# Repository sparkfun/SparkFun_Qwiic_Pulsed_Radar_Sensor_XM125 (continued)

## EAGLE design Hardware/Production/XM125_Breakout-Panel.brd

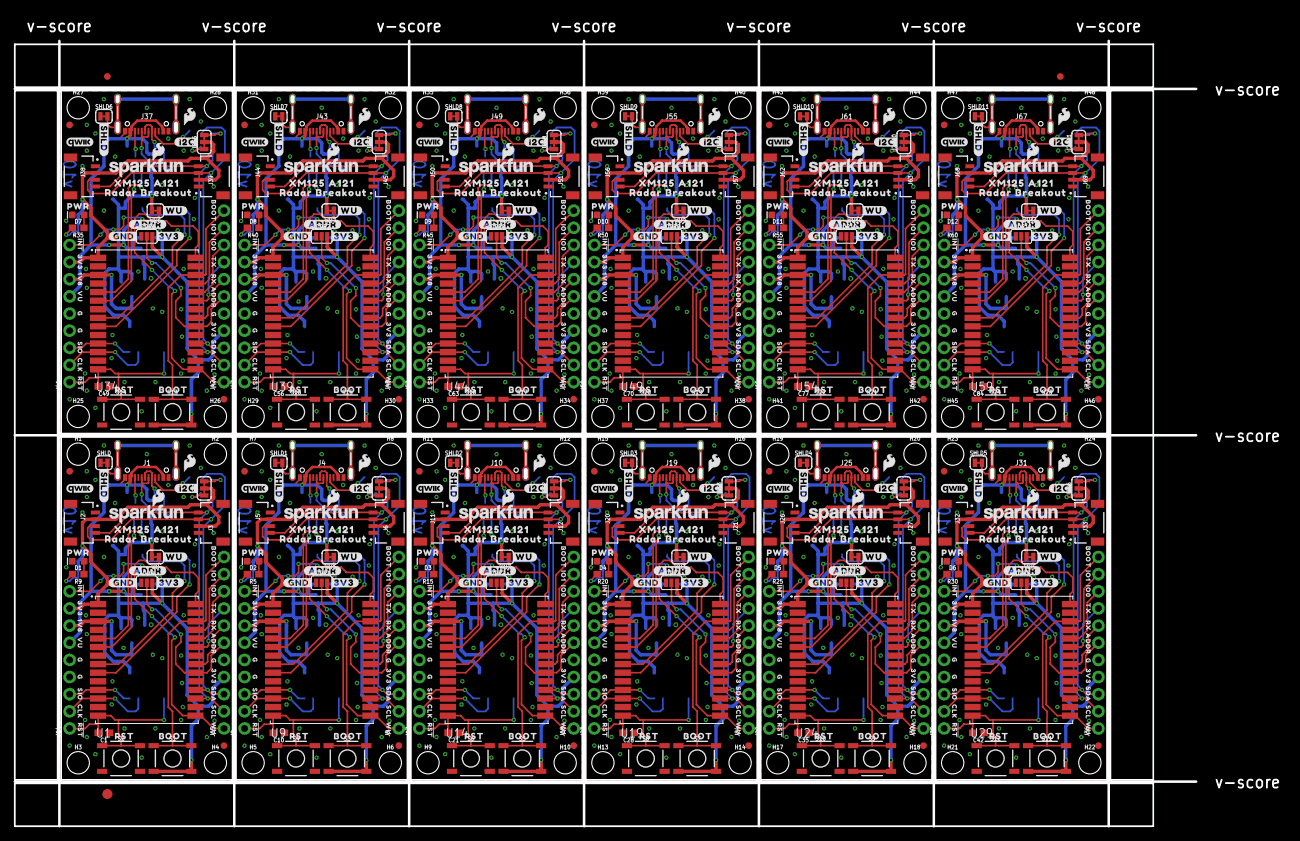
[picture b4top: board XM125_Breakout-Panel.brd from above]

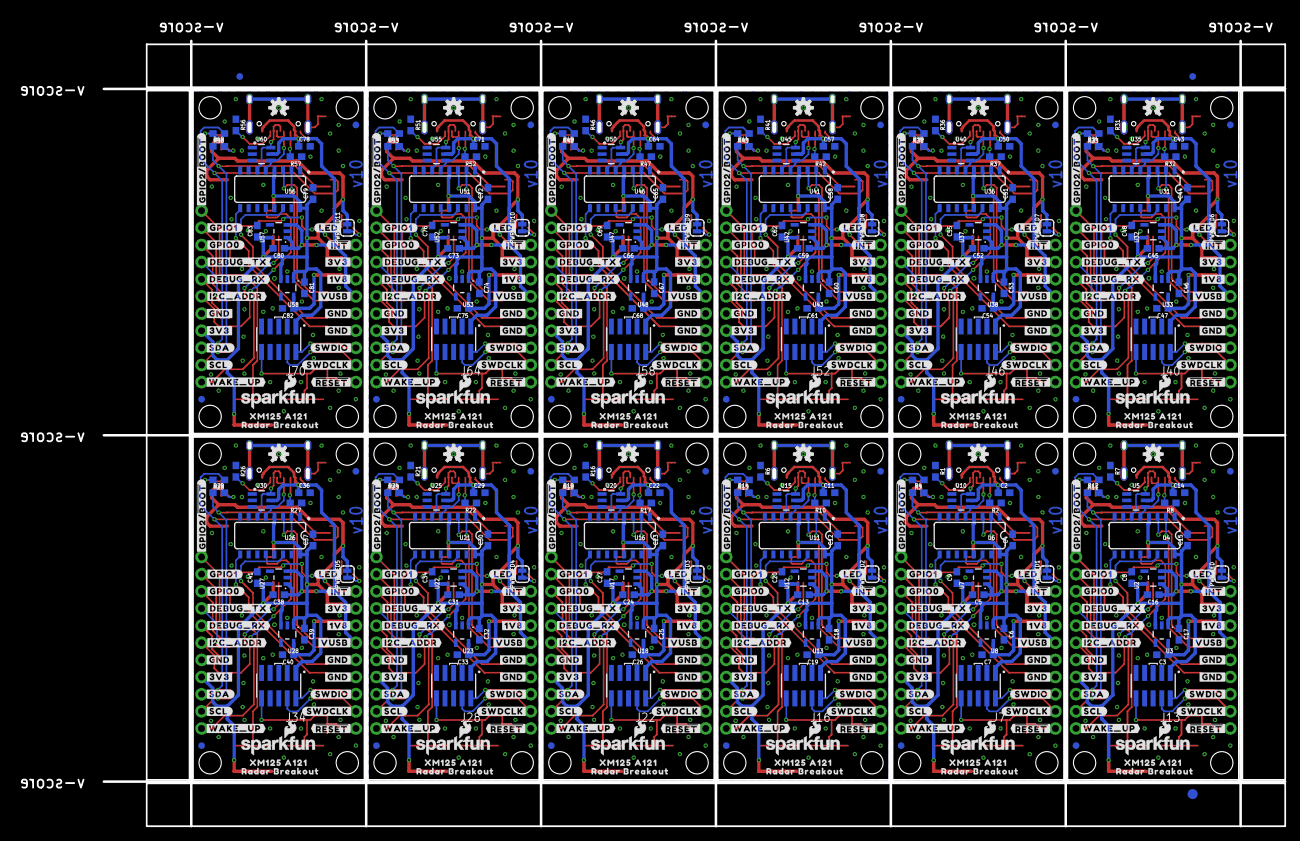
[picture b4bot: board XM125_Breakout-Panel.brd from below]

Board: 2 copper layers, 175.0 x 116.3 mm, 1182 parts (519 on the bottom side), 360 nets.

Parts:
ADDR, ADDR1, ADDR2, ADDR3, ADDR4, ADDR5, ADDR6, ADDR7, ADDR8, ADDR9, ADDR10, ADDR11: JUMPER-SMT_3_NO_SILK; SMT-JUMPER_3_NO_SILK
C1, C2, C4, C10, C11, C12, C14, C15, C21, C22, C23, C28, C29, C30, C35, C36, C37, C42, C43, C44, C49, C50, C51, C56, C57, C58, C63, C64, C65, C70, C71, C72, C77, C78, C79, C84: 0.1uF; 0603
C3, C7, C8, C9, C19, C20, C26, C27, C33, C34, C40, C41, C47, C48, C54, C55, C61, C62, C68, C69, C75, C76, C82, C83: 22uF; 0603
C5, C6, C13, C16, C17, C18, C24, C25, C31, C32, C38, C39, C45, C46, C52, C53, C59, C60, C66, C67, C73, C74, C80, C81: 2.2uF; 0603
D1, D2, D3, D4, D5, D6, D7, D8, D9, D10, D11, D12: Red; LED-0603
E$1, E$2, E$3, E$4: FIDUCIAL-1X2
E$5, E$6: FIDUCIAL-1.5X3
FD1, FD2, FD3, FD4, FD5, FD6, FD7, FD8, FD9, FD10, FD11, FD12, FD13, FD14, FD15, FD16, FD17, FD18, FD19, FD20, FD21, FD22, FD23, FD24, FD25, FD26, FD27, FD28, FD29, FD30, FD31, FD32, FD33, FD34, FD35, FD36, FD37, FD38, FD39, FD40, FD41, FD42, FD43, FD44, FD45, FD46, FD47, FD48: FIDUCIAL1X2; FIDUCIAL-1X2
H1, H2, H3, H4, H5, H6, H7, H8, H9, H10, H11, H12, H13, H14, H15, H16, H17, H18, H19, H20, H21, H22, H23, H24, H25, H26, H27, H28, H29, H30, H31, H32, H33, H34, H35, H36, H37, H38, H39, H40, H41, H42, H43, H44, H45, H46, H47, H48: STAND-OFF
I2C, I2C1, I2C2, I2C3, I2C4, I2C5, I2C6, I2C7, I2C8, I2C9, I2C10, I2C11: JUMPER-SMT_3_2-NC_TRACE_SILK; SMT-JUMPER_3_2-NC_TRACE_SILK
J1, J4, J10, J19, J25, J31, J37, J43, J49, J55, J61, J67: USB-C-16P-2LAYER-PADS
J2, J3, J5, J6, J11, J12, J20, J21, J26, J27, J32, J33, J38, J39, J44, J45, J50, J51, J56, J57, J62, J63, J68, J69: RIGHT_ANGLE; JST04_1MM_RA
J7, J13, J16, J22, J28, J34, J40, J46, J52, J58, J64, J70: SWD (DNP); 2X5-SMD-UNSHROUDED_DNP_NO_PASTE
J8, J14, J17, J23, J29, J35, J41, J47, J53, J59, J65, J71: 1X09_NO_SILK
J9, J15, J18, J24, J30, J36, J42, J48, J54, J60, J66, J72: 1X11_NO_SILK
LOGO1, LOGO2, LOGO11, LOGO16, LOGO21, LOGO26, LOGO31, LOGO36, LOGO41, LOGO46, LOGO51, LOGO56: QWIIC_LOGO_4MM; QWIIC_4MM
LOGO3, LOGO6, LOGO7, LOGO10, LOGO12, LOGO15, LOGO17, LOGO20, LOGO22, LOGO25, LOGO27, LOGO30, LOGO32, LOGO35, LOGO37, LOGO40, LOGO42, LOGO45, LOGO47, LOGO50, LOGO52, LOGO55, LOGO57, LOGO60: SFE_LOGO_NAME_FLAME.1_INCH; SFE_LOGO_NAME_FLAME_.1
LOGO4, LOGO8, LOGO13, LOGO18, LOGO23, LOGO28, LOGO33, LOGO38, LOGO43, LOGO48, LOGO53, LOGO58: OSHW-LOGOS; OSHW-LOGO-S
LOGO5, LOGO9, LOGO14, LOGO19, LOGO24, LOGO29, LOGO34, LOGO39, LOGO44, LOGO49, LOGO54, LOGO59: SFE_LOGO_FLAME.1_INCH; SFE_LOGO_FLAME_.1
PWR_LED, PWR_LED1, PWR_LED2, PWR_LED3, PWR_LED4, PWR_LED5, PWR_LED6, PWR_LED7, PWR_LED8, PWR_LED9, PWR_LED10, PWR_LED11: JUMPER-SMT_2_NC_TRACE_SILK; SMT-JUMPER_2_NC_TRACE_SILK
R1, R2, R6, R7, R8, R10, R16, R17, R21, R22, R26, R27, R31, R32, R36, R37, R41, R42, R46, R47, R51, R52, R56, R57: 5.1k; 0603
R3, R4, R11, R12, R13, R14, R18, R19, R23, R24, R28, R29, R33, R34, R38, R39, R43, R44, R48, R49, R53, R54, R58, R59: 2.2k; 0603
R5, R9, R15, R20, R25, R30, R35, R40, R45, R50, R55, R60: 4.7k; 0603
S1, S2, S3, S4, S5, S6, S7, S8, S9, S10, S11, S12, S13, S14, S15, S16, S17, S18, S19, S20, S21, S22, S23, S24: TACTILE_SWITCH_SMD_5.2MM
SHLD, SHLD1, SHLD2, SHLD3, SHLD4, SHLD5, SHLD6, SHLD7, SHLD8, SHLD9, SHLD10, SHLD11: JUMPER-SMT_2_NC_TRACE_SILK; SMT-JUMPER_2_NC_TRACE_SILK
U1, U9, U14, U19, U24, U29, U34, U39, U44, U49, U54, U59: XM125; XM125_ACC
U2, U7, U12, U17, U22, U27, U32, U37, U42, U47, U52, U57: RT9080-33GJ5; SOT23-5
U3, U8, U13, U18, U23, U28, U33, U38, U43, U48, U53, U58: RT9080-18GJ5; SOT23-5
U4, U6, U11, U16, U21, U26, U31, U36, U41, U46, U51, U56: CH340C; SO016
U5, U10, U15, U20, U25, U30, U35, U40, U45, U50, U55, U60: ESD Diode; SOT-23-6
U$1, U$72, U$126, U$180, U$234, U$288, U$342, U$396, U$450, U$504, U$558, U$612: #INT143
U$2, U$96, U$150, U$204, U$258, U$312, U$366, U$420, U$474, U$528, U$582, U$636: ##INT#2
U$3, U$64, U$118, U$172, U$226, U$280, U$334, U$388, U$442, U$496, U$550, U$604: #LED#139
U$4, U$30, U$31, U$68, U$69, U$70, U$122, U$123, U$124, U$176, U$177, U$178, U$230, U$231, U$232, U$284, U$285, U$286, U$338, U$339, U$340, U$392, U$393, U$394, U$446, U$447, U$448, U$500, U$501, U$502, U$554, U$555, U$556, U$608, U$609, U$610: #GND#141
U$5, U$52, U$110, U$164, U$218, U$272, U$326, U$380, U$434, U$488, U$542, U$596: RST1630063003525
U$6, U$85, U$139, U$193, U$247, U$301, U$355, U$409, U$463, U$517, U$571, U$625: RX1152
U$7, U$97, U$151, U$205, U$259, U$313, U$367, U$421, U$475, U$529, U$583, U$637: #SWDIO#4
U$8, U$95, U$149, U$203, U$257, U$311, U$365, U$419, U$473, U$527, U$581, U$635: #VUSB#1
U$9, U$105, U$159, U$213, U$267, U$321, U$375, U$429, U$483, U$537, U$591, U$645: #3V3#17
U$10, U$58, U$112, U$166, U$220, U$274, U$328, U$382, U$436, U$490, U$544, U$598: #SCL#8
U$11, U$37, U$109, U$163, U$217, U$271, U$325, U$379, U$433, U$487, U$541, U$595: BOOT21630063003532
U$12, U$57, U$111, U$165, U$219, U$273, U$327, U$381, U$435, U$489, U$543, U$597: PWR21630063003533
U$13, U$59, U$113, U$167, U$221, U$275, U$329, U$383, U$437, U$491, U$545, U$599: #SDA#9
U$14, U$33, U$73, U$75, U$127, U$129, U$181, U$183, U$235, U$237, U$289, U$291, U$343, U$345, U$397, U$399, U$451, U$453, U$505, U$507, U$559, U$561, U$613, U$615: 3V3144
U$15, U$74, U$128, U$182, U$236, U$290, U$344, U$398, U$452, U$506, U$560, U$614: 1V8144
U$16, U$67, U$121, U$175, U$229, U$283, U$337, U$391, U$445, U$499, U$553, U$607: #1V8#141
U$17, U$91, U$145, U$199, U$253, U$307, U$361, U$415, U$469, U$523, U$577, U$631: RADAR_BREAKOUT1163
U$18, U$99, U$153, U$207, U$261, U$315, U$369, U$423, U$477, U$531, U$585, U$639: WU9
U$19, U$98, U$152, U$206, U$260, U$314, U$368, U$422, U$476, U$530, U$584, U$638: #RST6
U$20, U$60, U$114, U$168, U$222, U$276, U$330, U$384, U$438, U$492, U$546, U$600: #GPIO0#5
U$21, U$61, U$115, U$169, U$223, U$277, U$331, U$385, U$439, U$493, U$547, U$601: #GPIO1#5
U$22, U$103, U$157, U$211, U$265, U$319, U$373, U$427, U$481, U$535, U$589, U$643: #WU#14
U$23, U$32, U$66, U$71, U$120, U$125, U$174, U$179, U$228, U$233, U$282, U$287, U$336, U$341, U$390, U$395, U$444, U$449, U$498, U$503, U$552, U$557, U$606, U$611: #3V3#141
U$24, U$92, U$146, U$200, U$254, U$308, U$362, U$416, U$470, U$524, U$578, U$632: XM125_A1211163
U$25, U$104, U$158, U$212, U$266, U$320, U$374, U$428, U$482, U$536, U$590, U$644: #ADDR#16
U$26, U$62, U$116, U$170, U$224, U$278, U$332, U$386, U$440, U$494, U$548, U$602: #I2C#126
U$27, U$65, U$119, U$173, U$227, U$281, U$335, U$389, U$443, U$497, U$551, U$605: #GPIO2##BOOT#141
U$28, U$108, U$162, U$216, U$270, U$324, U$378, U$432, U$486, U$540, U$594, U$648: #DEBUG_RX#19
U$29, U$63, U$117, U$171, U$225, U$279, U$333, U$387, U$441, U$495, U$549, U$603: #SHLD#129
U$34, U$35, U$36, U$76, U$77, U$78, U$130, U$131, U$132, U$184, U$185, U$186, U$238, U$239, U$240, U$292, U$293, U$294, U$346, U$347, U$348, U$400, U$401, U$402, U$454, U$455, U$456, U$508, U$509, U$510, U$562, U$563, U$564, U$616, U$617, U$618: G144
U$38, U$79, U$133, U$187, U$241, U$295, U$349, U$403, U$457, U$511, U$565, U$619: VU146
U$39, U$80, U$134, U$188, U$242, U$296, U$350, U$404, U$458, U$512, U$566, U$620: IO0147
U$40, U$81, U$135, U$189, U$243, U$297, U$351, U$405, U$459, U$513, U$567, U$621: IO1148
U$41, U$82, U$136, U$190, U$244, U$298, U$352, U$406, U$460, U$514, U$568, U$622: BOOT1149
U$42, U$83, U$137, U$191, U$245, U$299, U$353, U$407, U$461, U$515, U$569, U$623: CLK1150
U$43, U$84, U$138, U$192, U$246, U$300, U$354, U$408, U$462, U$516, U$570, U$624: #SWDCLK#1151
U$44, U$86, U$140, U$194, U$248, U$302, U$356, U$410, U$464, U$518, U$572, U$626: TX1153
U$45, U$87, U$141, U$195, U$249, U$303, U$357, U$411, U$465, U$519, U$573, U$627: ADDR1154
U$46, U$88, U$142, U$196, U$250, U$304, U$358, U$412, U$466, U$520, U$574, U$628: SDA1155
U$47, U$89, U$143, U$197, U$251, U$305, U$359, U$413, U$467, U$521, U$575, U$629: SCL1157
U$48, U$100, U$154, U$208, U$262, U$316, U$370, U$424, U$478, U$532, U$586, U$640: #I2C_ADDR#12
U$49, U$90, U$144, U$198, U$252, U$306, U$360, U$414, U$468, U$522, U$576, U$630: SIO1159
U$50, U$106, U$160, U$214, U$268, U$322, U$376, U$430, U$484, U$538, U$592, U$646: #GND#17
U$51, U$107, U$161, U$215, U$269, U$323, U$377, U$431, U$485, U$539, U$593, U$647: #DEBUG_TX#18
U$53, U$93, U$147, U$201, U$255, U$309, U$363, U$417, U$471, U$525, U$579, U$633: RADAR_BREAKOUT1166
U$54, U$94, U$148, U$202, U$256, U$310, U$364, U$418, U$472, U$526, U$580, U$634: XM125_A1211167
U$55, U$101, U$155, U$209, U$263, U$317, U$371, U$425, U$479, U$533, U$587, U$641: #WAKE_UP#12
U$56, U$102, U$156, U$210, U$264, U$318, U$372, U$426, U$480, U$534, U$588, U$642: ##RESET#13
WU, WU1, WU2, WU3, WU4, WU5, WU6, WU7, WU8, WU9, WU10, WU11: JUMPER-SMT_2_NC_TRACE_SILK; SMT-JUMPER_2_NC_TRACE_SILK

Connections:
1.8V: C3.1, J14.7, U1.3, U3.5
1.8V1: C7.1, J8.7, U8.5, U9.3
1.8V2: C19.1, J17.7, U13.5, U14.3
1.8V3: C26.1, J23.7, U18.5, U19.3
1.8V4: C33.1, J29.7, U23.5, U24.3
1.8V5: C40.1, J35.7, U28.5, U29.3
1.8V6: C47.1, J41.7, U33.5, U34.3
1.8V7: C54.1, J47.7, U38.5, U39.3
1.8V8: C61.1, J53.7, U43.5, U44.3
1.8V9: C68.1, J59.7, U48.5, U49.3
1.8V10: C75.1, J65.7, U53.5, U54.3
1.8V11: C82.1, J71.7, U58.5, U59.3
3.3V: ADDR.3, C8.1, C15.1, C17.1, I2C.2, J2.2, J3.2, J13.1, J14.8, J15.4, PWR_LED.2, S1.3, S1.4, U1.1, U2.5, U3.1, U3.3, U4.4, U4.16, WU.2
3.3V1: ADDR1.3, C4.1, C6.1, C9.1, I2C1.2, J5.2, J6.2, J7.1, J8.8, J9.4, PWR_LED1.2, S3.3, S3.4, U6.4, U6.16, U7.5, U8.1, U8.3, U9.1, WU1.2
3.3V2: ADDR2.3, C12.1, C18.1, C20.1, I2C2.2, J11.2, J12.2, J16.1, J17.8, J18.4, PWR_LED2.2, S5.3, S5.4, U11.4, U11.16, U12.5, U13.1, U13.3, U14.1, WU2.2
3.3V3: ADDR3.3, C23.1, C25.1, C27.1, I2C3.2, J20.2, J21.2, J22.1, J23.8, J24.4, PWR_LED3.2, S7.3, S7.4, U16.4, U16.16, U17.5, U18.1, U18.3, U19.1, WU3.2
3.3V4: ADDR4.3, C30.1, C32.1, C34.1, I2C4.2, J26.2, J27.2, J28.1, J29.8, J30.4, PWR_LED4.2, S9.3, S9.4, U21.4, U21.16, U22.5, U23.1, U23.3, U24.1, WU4.2
3.3V5: ADDR5.3, C37.1, C39.1, C41.1, I2C5.2, J32.2, J33.2, J34.1, J35.8, J36.4, PWR_LED5.2, S11.3, S11.4, U26.4, U26.16, U27.5, U28.1, U28.3, U29.1, WU5.2
3.3V6: ADDR6.3, C44.1, C46.1, C48.1, I2C6.2, J38.2, J39.2, J40.1, J41.8, J42.4, PWR_LED6.2, S13.3, S13.4, U31.4, U31.16, U32.5, U33.1, U33.3, U34.1, WU6.2
3.3V7: ADDR7.3, C51.1, C53.1, C55.1, I2C7.2, J44.2, J45.2, J46.1, J47.8, J48.4, PWR_LED7.2, S15.3, S15.4, U36.4, U36.16, U37.5, U38.1, U38.3, U39.1, WU7.2
3.3V8: ADDR8.3, C58.1, C60.1, C62.1, I2C8.2, J50.2, J51.2, J52.1, J53.8, J54.4, PWR_LED8.2, S17.3, S17.4, U41.4, U41.16, U42.5, U43.1, U43.3, U44.1, WU8.2
3.3V9: ADDR9.3, C65.1, C67.1, C69.1, I2C9.2, J56.2, J57.2, J58.1, J59.8, J60.4, PWR_LED9.2, S19.3, S19.4, U46.4, U46.16, U47.5, U48.1, U48.3, U49.1, WU9.2
3.3V10: ADDR10.3, C72.1, C74.1, C76.1, I2C10.2, J62.2, J63.2, J64.1, J65.8, J66.4, PWR_LED10.2, S21.3, S21.4, U51.4, U51.16, U52.5, U53.1, U53.3, U54.1, WU10.2
3.3V11: ADDR11.3, C79.1, C81.1, C83.1, I2C11.2, J68.2, J69.2, J70.1, J71.8, J72.4, PWR_LED11.2, S23.3, S23.4, U56.4, U56.16, U57.5, U58.1, U58.3, U59.1, WU11.2
!XM125_INT: J14.9, U1.28
!XM125_INT1: J8.9, U9.28
!XM125_INT2: J17.9, U14.28
!XM125_INT3: J23.9, U19.28
!XM125_INT4: J29.9, U24.28
!XM125_INT5: J35.9, U29.28
!XM125_INT6: J41.9, U34.28
!XM125_INT7: J47.9, U39.28
!XM125_INT8: J53.9, U44.28
!XM125_INT9: J59.9, U49.28
!XM125_INT10: J65.9, U54.28
!XM125_INT11: J71.9, U59.28
!XM125_RESET: C1.2, J13.10, J14.1, S2.1, S2.2, U1.14
!XM125_RESET1: C10.2, J7.10, J8.1, S4.1, S4.2, U9.14
!XM125_RESET2: C21.2, J16.10, J17.1, S6.1, S6.2, U14.14
!XM125_RESET3: C28.2, J22.10, J23.1, S8.1, S8.2, U19.14
!XM125_RESET4: C35.2, J28.10, J29.1, S10.1, S10.2, U24.14
!XM125_RESET5: C42.2, J34.10, J35.1, S12.1, S12.2, U29.14
!XM125_RESET6: C49.2, J40.10, J41.1, S14.1, S14.2, U34.14
!XM125_RESET7: C56.2, J46.10, J47.1, S16.1, S16.2, U39.14
!XM125_RESET8: C63.2, J52.10, J53.1, S18.1, S18.2, U44.14
!XM125_RESET9: C70.2, J58.10, J59.1, S20.1, S20.2, U49.14
!XM125_RESET10: C77.2, J64.10, J65.1, S22.1, S22.2, U54.14
!XM125_RESET11: C84.2, J70.10, J71.1, S24.1, S24.2, U59.14
CH340-CTS: U1.9, U4.9
CH340-CTS1: U6.9, U9.9
CH340-CTS2: U11.9, U14.9
CH340-CTS3: U16.9, U19.9
CH340-CTS4: U21.9, U24.9
CH340-CTS5: U26.9, U29.9
CH340-CTS6: U31.9, U34.9
CH340-CTS7: U36.9, U39.9
CH340-CTS8: U41.9, U44.9
CH340-CTS9: U46.9, U49.9
CH340-CTS10: U51.9, U54.9
CH340-CTS11: U56.9, U59.9
CH340-RTS: U1.8, U4.14
CH340-RTS1: U6.14, U9.8
CH340-RTS2: U11.14, U14.8
CH340-RTS3: U16.14, U19.8
CH340-RTS4: U21.14, U24.8
CH340-RTS5: U26.14, U29.8
CH340-RTS6: U31.14, U34.8
CH340-RTS7: U36.14, U39.8
CH340-RTS8: U41.14, U44.8
CH340-RTS9: U46.14, U49.8
CH340-RTS10: U51.14, U54.8
CH340-RTS11: U56.14, U59.8
CH340-RX: U1.5, U4.3
CH340-RX1: U6.3, U9.5
CH340-RX2: U11.3, U14.5
CH340-RX3: U16.3, U19.5
CH340-RX4: U21.3, U24.5
CH340-RX5: U26.3, U29.5
CH340-RX6: U31.3, U34.5
CH340-RX7: U36.3, U39.5
CH340-RX8: U41.3, U44.5
CH340-RX9: U46.3, U49.5
CH340-RX10: U51.3, U54.5
CH340-RX11: U56.3, U59.5
CH340-TX: U1.6, U4.2
CH340-TX1: U6.2, U9.6
CH340-TX2: U11.2, U14.6
CH340-TX3: U16.2, U19.6
CH340-TX4: U21.2, U24.6
CH340-TX5: U26.2, U29.6
CH340-TX6: U31.2, U34.6
CH340-TX7: U36.2, U39.6
CH340-TX8: U41.2, U44.6
CH340-TX9: U46.2, U49.6
CH340-TX10: U51.2, U54.6
CH340-TX11: U56.2, U59.6
DEBUG_UART-RX: J15.7, U1.21
DEBUG_UART-RX1: J9.7, U9.21
DEBUG_UART-RX2: J18.7, U14.21
DEBUG_UART-RX3: J24.7, U19.21
DEBUG_UART-RX4: J30.7, U24.21
DEBUG_UART-RX5: J36.7, U29.21
DEBUG_UART-RX6: J42.7, U34.21
DEBUG_UART-RX7: J48.7, U39.21
DEBUG_UART-RX8: J54.7, U44.21
DEBUG_UART-RX9: J60.7, U49.21
DEBUG_UART-RX10: J66.7, U54.21
DEBUG_UART-RX11: J72.7, U59.21
DEBUG_UART-TX: J15.8, U1.23
DEBUG_UART-TX1: J9.8, U9.23
DEBUG_UART-TX2: J18.8, U14.23
DEBUG_UART-TX3: J24.8, U19.23
DEBUG_UART-TX4: J30.8, U24.23
DEBUG_UART-TX5: J36.8, U29.23
DEBUG_UART-TX6: J42.8, U34.23
DEBUG_UART-TX7: J48.8, U39.23
DEBUG_UART-TX8: J54.8, U44.23
DEBUG_UART-TX9: J60.8, U49.23
DEBUG_UART-TX10: J66.8, U54.23
DEBUG_UART-TX11: J72.8, U59.23
GND: ADDR.1, C1.1, C3.2, C8.2, C14.2, C15.2, C16.2, C17.2, D1.C, J1.GND, J1.GND2, J2.1, J3.1, J13.3, J13.5, J13.9, J14.4, J14.5, J15.5, R7.1, R8.1, S2.3, S2.4, SHLD.1, U1.2, U1.4, U1.7, U1.10, U1.13, U1.16, U1.19, U1.22, U1.27, U2.2, U3.2, U4.1, U5.2
GND1: ADDR1.1, C2.2, C4.2, C5.2, C6.2, C7.2, C9.2, C10.1, D2.C, J4.GND, J4.GND2, J5.1, J6.1, J7.3, J7.5, J7.9, J8.4, J8.5, J9.5, R1.1, R2.1, S4.3, S4.4, SHLD1.1, U6.1, U7.2, U8.2, U9.2, U9.4, U9.7, U9.10, U9.13, U9.16, U9.19, U9.22, U9.27, U10.2
GND2: ADDR2.1, C11.2, C12.2, C13.2, C18.2, C19.2, C20.2, C21.1, D3.C, J10.GND, J10.GND2, J11.1, J12.1, J16.3, J16.5, J16.9, J17.4, J17.5, J18.5, R6.1, R10.1, S6.3, S6.4, SHLD2.1, U11.1, U12.2, U13.2, U14.2, U14.4, U14.7, U14.10, U14.13, U14.16, U14.19, U14.22, U14.27, U15.2
GND3: ADDR3.1, C22.2, C23.2, C24.2, C25.2, C26.2, C27.2, C28.1, D4.C, J19.GND, J19.GND2, J20.1, J21.1, J22.3, J22.5, J22.9, J23.4, J23.5, J24.5, R16.1, R17.1, S8.3, S8.4, SHLD3.1, U16.1, U17.2, U18.2, U19.2, U19.4, U19.7, U19.10, U19.13, U19.16, U19.19, U19.22, U19.27, U20.2
GND4: ADDR4.1, C29.2, C30.2, C31.2, C32.2, C33.2, C34.2, C35.1, D5.C, J25.GND, J25.GND2, J26.1, J27.1, J28.3, J28.5, J28.9, J29.4, J29.5, J30.5, R21.1, R22.1, S10.3, S10.4, SHLD4.1, U21.1, U22.2, U23.2, U24.2, U24.4, U24.7, U24.10, U24.13, U24.16, U24.19, U24.22, U24.27, U25.2
GND5: ADDR5.1, C36.2, C37.2, C38.2, C39.2, C40.2, C41.2, C42.1, D6.C, J31.GND, J31.GND2, J32.1, J33.1, J34.3, J34.5, J34.9, J35.4, J35.5, J36.5, R26.1, R27.1, S12.3, S12.4, SHLD5.1, U26.1, U27.2, U28.2, U29.2, U29.4, U29.7, U29.10, U29.13, U29.16, U29.19, U29.22, U29.27, U30.2
GND6: ADDR6.1, C43.2, C44.2, C45.2, C46.2, C47.2, C48.2, C49.1, D7.C, J37.GND, J37.GND2, J38.1, J39.1, J40.3, J40.5, J40.9, J41.4, J41.5, J42.5, R31.1, R32.1, S14.3, S14.4, SHLD6.1, U31.1, U32.2, U33.2, U34.2, U34.4, U34.7, U34.10, U34.13, U34.16, U34.19, U34.22, U34.27, U35.2
GND7: ADDR7.1, C50.2, C51.2, C52.2, C53.2, C54.2, C55.2, C56.1, D8.C, J43.GND, J43.GND2, J44.1, J45.1, J46.3, J46.5, J46.9, J47.4, J47.5, J48.5, R36.1, R37.1, S16.3, S16.4, SHLD7.1, U36.1, U37.2, U38.2, U39.2, U39.4, U39.7, U39.10, U39.13, U39.16, U39.19, U39.22, U39.27, U40.2
GND8: ADDR8.1, C57.2, C58.2, C59.2, C60.2, C61.2, C62.2, C63.1, D9.C, J49.GND, J49.GND2, J50.1, J51.1, J52.3, J52.5, J52.9, J53.4, J53.5, J54.5, R41.1, R42.1, S18.3, S18.4, SHLD8.1, U41.1, U42.2, U43.2, U44.2, U44.4, U44.7, U44.10, U44.13, U44.16, U44.19, U44.22, U44.27, U45.2
GND9: ADDR9.1, C64.2, C65.2, C66.2, C67.2, C68.2, C69.2, C70.1, D10.C, J55.GND, J55.GND2, J56.1, J57.1, J58.3, J58.5, J58.9, J59.4, J59.5, J60.5, R46.1, R47.1, S20.3, S20.4, SHLD9.1, U46.1, U47.2, U48.2, U49.2, U49.4, U49.7, U49.10, U49.13, U49.16, U49.19, U49.22, U49.27, U50.2
GND10: ADDR10.1, C71.2, C72.2, C73.2, C74.2, C75.2, C76.2, C77.1, D11.C, J61.GND, J61.GND2, J62.1, J63.1, J64.3, J64.5, J64.9, J65.4, J65.5, J66.5, R51.1, R52.1, S22.3, S22.4, SHLD10.1, U51.1, U52.2, U53.2, U54.2, U54.4, U54.7, U54.10, U54.13, U54.16, U54.19, U54.22, U54.27, U55.2
GND11: ADDR11.1, C78.2, C79.2, C80.2, C81.2, C82.2, C83.2, C84.1, D12.C, J67.GND, J67.GND2, J68.1, J69.1, J70.3, J70.5, J70.9, J71.4, J71.5, J72.5, R56.1, R57.1, S24.3, S24.4, SHLD11.1, U56.1, U57.2, U58.2, U59.2, U59.4, U59.7, U59.10, U59.13, U59.16, U59.19, U59.22, U59.27, U60.2
unnamed: J1.A6, J1.B6, U4.5, U5.4
unnamed: J1.A7, J1.B7, U4.6, U5.6
unnamed: J4.A6, J4.B6, U6.5, U10.4
unnamed: J4.A7, J4.B7, U6.6, U10.6
unnamed: J4.SHLD1, J4.SHLD2, J4.SHLD3, J4.SHLD4, SHLD1.2
unnamed: J4.B5, R2.2
unnamed: J4.A5, R1.2
unnamed: PWR_LED1.1, R5.2
unnamed: J1.SHLD1, J1.SHLD2, J1.SHLD3, J1.SHLD4, SHLD.2
unnamed: J1.B5, R8.2
unnamed: J1.A5, R7.2
unnamed: D2.A, R5.1
unnamed: I2C1.3, R3.2
unnamed: PWR_LED.1, R9.2
unnamed: D1.A, R9.1
unnamed: I2C.3, R11.2
unnamed: I2C.1, R12.2
unnamed: I2C1.1, R4.2
unnamed: J10.A6, J10.B6, U11.5, U15.4
unnamed: J10.A7, J10.B7, U11.6, U15.6
unnamed: J10.SHLD1, J10.SHLD2, J10.SHLD3, J10.SHLD4, SHLD2.2
unnamed: J10.B5, R10.2
unnamed: J10.A5, R6.2
unnamed: PWR_LED2.1, R15.2
unnamed: D3.A, R15.1
unnamed: I2C2.3, R13.2
unnamed: I2C2.1, R14.2
unnamed: J19.A6, J19.B6, U16.5, U20.4
unnamed: J19.A7, J19.B7, U16.6, U20.6
unnamed: J19.SHLD1, J19.SHLD2, J19.SHLD3, J19.SHLD4, SHLD3.2
unnamed: J19.B5, R17.2
unnamed: J19.A5, R16.2
unnamed: PWR_LED3.1, R20.2
unnamed: D4.A, R20.1
unnamed: I2C3.3, R18.2
unnamed: I2C3.1, R19.2
unnamed: J25.A6, J25.B6, U21.5, U25.4
unnamed: J25.A7, J25.B7, U21.6, U25.6
unnamed: J25.SHLD1, J25.SHLD2, J25.SHLD3, J25.SHLD4, SHLD4.2
unnamed: J25.B5, R22.2
unnamed: J25.A5, R21.2
unnamed: PWR_LED4.1, R25.2
unnamed: D5.A, R25.1
unnamed: I2C4.3, R23.2
unnamed: I2C4.1, R24.2
unnamed: J31.A6, J31.B6, U26.5, U30.4
unnamed: J31.A7, J31.B7, U26.6, U30.6
unnamed: J31.SHLD1, J31.SHLD2, J31.SHLD3, J31.SHLD4, SHLD5.2
unnamed: J31.B5, R27.2
unnamed: J31.A5, R26.2
unnamed: PWR_LED5.1, R30.2
unnamed: D6.A, R30.1
unnamed: I2C5.3, R28.2
unnamed: I2C5.1, R29.2
unnamed: J37.A6, J37.B6, U31.5, U35.4
unnamed: J37.A7, J37.B7, U31.6, U35.6
unnamed: J37.SHLD1, J37.SHLD2, J37.SHLD3, J37.SHLD4, SHLD6.2
unnamed: J37.B5, R32.2
unnamed: J37.A5, R31.2
unnamed: PWR_LED6.1, R35.2
unnamed: D7.A, R35.1
unnamed: I2C6.3, R33.2
unnamed: I2C6.1, R34.2
unnamed: J43.A6, J43.B6, U36.5, U40.4
unnamed: J43.A7, J43.B7, U36.6, U40.6
unnamed: J43.SHLD1, J43.SHLD2, J43.SHLD3, J43.SHLD4, SHLD7.2
unnamed: J43.B5, R37.2
unnamed: J43.A5, R36.2
unnamed: PWR_LED7.1, R40.2
unnamed: D8.A, R40.1
unnamed: I2C7.3, R38.2
unnamed: I2C7.1, R39.2
unnamed: J49.A6, J49.B6, U41.5, U45.4
unnamed: J49.A7, J49.B7, U41.6, U45.6
unnamed: J49.SHLD1, J49.SHLD2, J49.SHLD3, J49.SHLD4, SHLD8.2
unnamed: J49.B5, R42.2
unnamed: J49.A5, R41.2
unnamed: PWR_LED8.1, R45.2
unnamed: D9.A, R45.1
unnamed: I2C8.3, R43.2
unnamed: I2C8.1, R44.2
unnamed: J55.A6, J55.B6, U46.5, U50.4
unnamed: J55.A7, J55.B7, U46.6, U50.6
unnamed: J55.SHLD1, J55.SHLD2, J55.SHLD3, J55.SHLD4, SHLD9.2
unnamed: J55.B5, R47.2
unnamed: J55.A5, R46.2
unnamed: PWR_LED9.1, R50.2
unnamed: D10.A, R50.1
unnamed: I2C9.3, R48.2
unnamed: I2C9.1, R49.2
unnamed: J61.A6, J61.B6, U51.5, U55.4
unnamed: J61.A7, J61.B7, U51.6, U55.6
unnamed: J61.SHLD1, J61.SHLD2, J61.SHLD3, J61.SHLD4, SHLD10.2
unnamed: J61.B5, R52.2
unnamed: J61.A5, R51.2
unnamed: PWR_LED10.1, R55.2
unnamed: D11.A, R55.1
unnamed: I2C10.3, R53.2
unnamed: I2C10.1, R54.2
unnamed: J67.A6, J67.B6, U56.5, U60.4
unnamed: J67.A7, J67.B7, U56.6, U60.6
unnamed: J67.SHLD1, J67.SHLD2, J67.SHLD3, J67.SHLD4, SHLD11.2
unnamed: J67.B5, R57.2
unnamed: J67.A5, R56.2
unnamed: PWR_LED11.1, R60.2
unnamed: D12.A, R60.1
unnamed: I2C11.3, R58.2
unnamed: I2C11.1, R59.2
SCL: J2.4, J3.4, J15.2, R12.1, U1.17
SCL1: J5.4, J6.4, J9.2, R4.1, U9.17
SCL2: J11.4, J12.4, J18.2, R14.1, U14.17
SCL3: J20.4, J21.4, J24.2, R19.1, U19.17
SCL4: J26.4, J27.4, J30.2, R24.1, U24.17
SCL5: J32.4, J33.4, J36.2, R29.1, U29.17
SCL6: J38.4, J39.4, J42.2, R34.1, U34.17
SCL7: J44.4, J45.4, J48.2, R39.1, U39.17
SCL8: J50.4, J51.4, J54.2, R44.1, U44.17
SCL9: J56.4, J57.4, J60.2, R49.1, U49.17
SCL10: J62.4, J63.4, J66.2, R54.1, U54.17
SCL11: J68.4, J69.4, J72.2, R59.1, U59.17
SDA: J2.3, J3.3, J15.3, R11.1, U1.18
SDA1: J5.3, J6.3, J9.3, R3.1, U9.18
SDA2: J11.3, J12.3, J18.3, R13.1, U14.18
SDA3: J20.3, J21.3, J24.3, R18.1, U19.18
SDA4: J26.3, J27.3, J30.3, R23.1, U24.18
SDA5: J32.3, J33.3, J36.3, R28.1, U29.18
SDA6: J38.3, J39.3, J42.3, R33.1, U34.18
SDA7: J44.3, J45.3, J48.3, R38.1, U39.18
SDA8: J50.3, J51.3, J54.3, R43.1, U44.18
SDA9: J56.3, J57.3, J60.3, R48.1, U49.18
SDA10: J62.3, J63.3, J66.3, R53.1, U54.18
SDA11: J68.3, J69.3, J72.3, R58.1, U59.18
SWD_CLK: J13.4, J14.2, U1.12
SWD_CLK1: J7.4, J8.2, U9.12
SWD_CLK2: J16.4, J17.2, U14.12
SWD_CLK3: J22.4, J23.2, U19.12
SWD_CLK4: J28.4, J29.2, U24.12
SWD_CLK5: J34.4, J35.2, U29.12
SWD_CLK6: J40.4, J41.2, U34.12
SWD_CLK7: J46.4, J47.2, U39.12
SWD_CLK8: J52.4, J53.2, U44.12
SWD_CLK9: J58.4, J59.2, U49.12
SWD_CLK10: J64.4, J65.2, U54.12
SWD_CLK11: J70.4, J71.2, U59.12
SWD_IO: J13.2, J14.3, U1.11
SWD_IO1: J7.2, J8.3, U9.11
SWD_IO2: J16.2, J17.3, U14.11
SWD_IO3: J22.2, J23.3, U19.11
SWD_IO4: J28.2, J29.3, U24.11
SWD_IO5: J34.2, J35.3, U29.11
SWD_IO6: J40.2, J41.3, U34.11
SWD_IO7: J46.2, J47.3, U39.11
SWD_IO8: J52.2, J53.3, U44.11
SWD_IO9: J58.2, J59.3, U49.11
SWD_IO10: J64.2, J65.3, U54.11
SWD_IO11: J70.2, J71.3, U59.11
V_USB: C14.1, C16.1, J1.VBUS1, J1.VBUS2, J14.6, U2.1, U2.3, U5.5
V_USB1: C2.1, C5.1, J4.VBUS1, J4.VBUS2, J8.6, U7.1, U7.3, U10.5
V_USB2: C11.1, C13.1, J10.VBUS1, J10.VBUS2, J17.6, U12.1, U12.3, U15.5
V_USB3: C22.1, C24.1, J19.VBUS1, J19.VBUS2, J23.6, U17.1, U17.3, U20.5
V_USB4: C29.1, C31.1, J25.VBUS1, J25.VBUS2, J29.6, U22.1, U22.3, U25.5
V_USB5: C36.1, C38.1, J31.VBUS1, J31.VBUS2, J35.6, U27.1, U27.3, U30.5
V_USB6: C43.1, C45.1, J37.VBUS1, J37.VBUS2, J41.6, U32.1, U32.3, U35.5
V_USB7: C50.1, C52.1, J43.VBUS1, J43.VBUS2, J47.6, U37.1, U37.3, U40.5
V_USB8: C57.1, C59.1, J49.VBUS1, J49.VBUS2, J53.6, U42.1, U42.3, U45.5
V_USB9: C64.1, C66.1, J55.VBUS1, J55.VBUS2, J59.6, U47.1, U47.3, U50.5
V_USB10: C71.1, C73.1, J61.VBUS1, J61.VBUS2, J65.6, U52.1, U52.3, U55.5
V_USB11: C78.1, C80.1, J67.VBUS1, J67.VBUS2, J71.6, U57.1, U57.3, U60.5
WAKE_UP: J15.1, U1.15, WU.1
WAKE_UP1: J9.1, U9.15, WU1.1
WAKE_UP2: J18.1, U14.15, WU2.1
WAKE_UP3: J24.1, U19.15, WU3.1
WAKE_UP4: J30.1, U24.15, WU4.1
WAKE_UP5: J36.1, U29.15, WU5.1
WAKE_UP6: J42.1, U34.15, WU6.1
WAKE_UP7: J48.1, U39.15, WU7.1
WAKE_UP8: J54.1, U44.15, WU8.1
WAKE_UP9: J60.1, U49.15, WU9.1
WAKE_UP10: J66.1, U54.15, WU10.1
WAKE_UP11: J72.1, U59.15, WU11.1
XM125_GPIO0: J15.9, U1.24
XM125_GPIO1: J15.10, U1.25
XM125_GPIO2: J9.10, U9.25
XM125_GPIO2/BOOT0: J15.11, S1.1, S1.2, U1.26
XM125_GPIO2/BOOT1: J9.11, S3.1, S3.2, U9.26
XM125_GPIO2/BOOT2: J18.11, S5.1, S5.2, U14.26
XM125_GPIO2/BOOT3: J24.11, S7.1, S7.2, U19.26
XM125_GPIO2/BOOT4: J30.11, S9.1, S9.2, U24.26
XM125_GPIO2/BOOT5: J36.11, S11.1, S11.2, U29.26
XM125_GPIO2/BOOT6: J42.11, S13.1, S13.2, U34.26
XM125_GPIO2/BOOT7: J48.11, S15.1, S15.2, U39.26
XM125_GPIO2/BOOT8: J54.11, S17.1, S17.2, U44.26
XM125_GPIO2/BOOT9: J60.11, S19.1, S19.2, U49.26
XM125_GPIO2/BOOT10: J66.11, S21.1, S21.2, U54.26
XM125_GPIO2/BOOT11: J72.11, S23.1, S23.2, U59.26
XM125_GPIO3: J9.9, U9.24
XM125_GPIO4: J18.10, U14.25
XM125_GPIO5: J18.9, U14.24
XM125_GPIO6: J24.10, U19.25
XM125_GPIO7: J24.9, U19.24
XM125_GPIO8: J30.10, U24.25
XM125_GPIO9: J30.9, U24.24
XM125_GPIO10: J36.10, U29.25
XM125_GPIO11: J36.9, U29.24
XM125_GPIO12: J42.10, U34.25
XM125_GPIO13: J42.9, U34.24
XM125_GPIO14: J48.10, U39.25
XM125_GPIO15: J48.9, U39.24
XM125_GPIO16: J54.10, U44.25
XM125_GPIO17: J54.9, U44.24
XM125_GPIO18: J60.10, U49.25
XM125_GPIO19: J60.9, U49.24
XM125_GPIO20: J66.10, U54.25
XM125_GPIO21: J66.9, U54.24
XM125_GPIO22: J72.10, U59.25
XM125_GPIO23: J72.9, U59.24
XM125_I2C_ADDRESS: ADDR.2, J15.6, U1.20
XM125_I2C_ADDRESS1: ADDR1.2, J9.6, U9.20
XM125_I2C_ADDRESS2: ADDR2.2, J18.6, U14.20
XM125_I2C_ADDRESS3: ADDR3.2, J24.6, U19.20
XM125_I2C_ADDRESS4: ADDR4.2, J30.6, U24.20
XM125_I2C_ADDRESS5: ADDR5.2, J36.6, U29.20
XM125_I2C_ADDRESS6: ADDR6.2, J42.6, U34.20
XM125_I2C_ADDRESS7: ADDR7.2, J48.6, U39.20
XM125_I2C_ADDRESS8: ADDR8.2, J54.6, U44.20
XM125_I2C_ADDRESS9: ADDR9.2, J60.6, U49.20
XM125_I2C_ADDRESS10: ADDR10.2, J66.6, U54.20
XM125_I2C_ADDRESS11: ADDR11.2, J72.6, U59.20

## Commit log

2023-10-26 Added user guide and removed unneeded folders
    Initial commit of the repo!
2023-10-27 Added datasheet
2023-11-03 Added binaries needed for software
    This is simply a download of the software needed to run the evaluation board
2023-11-10 Addition of XM125 SDK files
    Pulled from Acconeer's website as a download - full credits will be given where due.
2023-11-10 Further documentation added
2023-11-15 Addition of initial Hardware files for breakout
    We will be doing a breakout with this board, no need for 1x1 and thing+ breakout files. Will be keeping until official product definition is given
2023-11-15 Library part completed
    Adjusted the file structure name to no longer have a space in it. Finished the library part for the schematic
2023-12-05 Removed uneeded board files; updates to breakout board
    Removed the 1x1 and Thing+ board options; updated the schematic and layout - grouped together the needed sections in the layout
2023-12-06 Addition of further documentation; initial schematic ready for review
    Fixed small issues on schematic; added I2C documentation to the repo
2023-12-11 Updates as per schematic review
    For full detailed list of changes, see XM125 Schematic review document
2023-12-18 Updated files for design review
    Nearing completion and ready for design review - completed layout, added measures, added labels, name, logos
2023-12-18 Slight aesthetic change - ready for review!
    Ready for protos review
2023-12-19 Changes from design review
    Final changes made - ready for re-review one last time before ordering protos
    For full list of changes, see Protos Review document
2023-12-21 Production files added
2024-01-18 Added specific firmware for presence and distance sensing
    All of the XM125 firmware was broken up into presence and distance - will be uploading distance sensing onto device initially
2024-01-23 Initial commit for v10 red boards; adjusted firmware files
    Small changes made for board - removed EN pullups, changed button part number; no need for distance and presence file differentiation - just run with binaries in the original SDK; added STM32CubeIDEP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
2024-02-07 Changes for reds review completed; panel files added
    Changes for review have been made; panelized files have been added
2024-02-08 Cleanup repo; design review changes
    Check design review document for full list of changes/details.
2024-02-08 Final changes; reds ready for ordering!
    Finished up Dryw's comments: see google doc for more information on specific changes made; panelized files updated and ready for ordering
2024-03-22 Initial Push Hookup Guide
2024-03-29 Add Python Exploration Tool, Rearrange Sections, Add Product Video
2024-04-02 Add clarification on range
2024-04-02 Add notes for clarification on range in Arduino Examples
2024-04-11 Add Additional Step, Troubleshooting Tips, and CSS fix
    - Move troubleshooting tip from STM32CubeProgrammer Section to Troubleshooting section
    - Add additional step to configure COM port when connecting Acconeer Exploration Tool
    - Add errors in Troubleshooting section
    - Add Wes' fix to enable word/line wrap in code blocks
2024-04-11 Deployed e60db5a with MkDocs version: 1.5.3
2024-10-28 Add cookies
2024-10-29 Deployed 224afa9 with MkDocs version: 1.6.1
2025-02-20 Update introduction.md
    Fixing missing image
2025-02-20 Deployed 0b48c06 with MkDocs version: 1.6.1
2026-06-03 Deployed a049212 with MkDocs version: 1.6.1
